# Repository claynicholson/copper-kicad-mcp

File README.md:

<!-- mcp-name: io.github.claynicholson/copper -->
# copper-kicad-mcp

Copper connects your AI app to KiCad, so it can design real boards you can order: schematic, LCSC parts, PCB
layout and routing, KiCad's own ERC and DRC, renders and JLCPCB fab files.

## Install

You need [KiCad 10](https://www.kicad.org/download/). Then pick one:

| You use | Do this |
|---|---|
| Windows, any AI app | Run `Copper-for-KiCad-1.1.1-Setup.exe` from the [latest release](https://github.com/claynicholson/copper-kicad-mcp/releases/latest) and tick your AI apps |
| Claude Desktop | Double-click `copper-1.1.1.mcpb` from the [latest release](https://github.com/claynicholson/copper-kicad-mcp/releases/latest) |
| Claude Code | The two plugin commands below |
| Cursor, VS Code, Windsurf, Codex, Zed and others | `npx -y copper-kicad setup` (Node.js 18+), or [add to Cursor](https://cursor.com/install-mcp?name=copper&config=eyJjb21tYW5kIjoibnB4IiwiYXJncyI6WyIteSIsImNvcHBlci1raWNhZCJdfQ%3D%3D) / [install in VS Code](https://vscode.dev/redirect/mcp/install?name=copper&config=%7B%22command%22%3A%22npx%22%2C%22args%22%3A%5B%22-y%22%2C%22copper-kicad%22%5D%7D) |
| A terminal | The one-line installer below |

```sh
# Claude Code
claude plugin marketplace add claynicholson/copper-kicad-mcp
claude plugin install copper@copper
```

```powershell
# Windows (PowerShell)
powershell -ExecutionPolicy Bypass -c "irm https://raw.githubusercontent.com/claynicholson/copper-kicad-mcp/main/installer/install.ps1 | iex"
```

```sh
# macOS / Linux
curl -LsSf https://raw.githubusercontent.com/claynicholson/copper-kicad-mcp/main/installer/install.sh | sh
```

Windows is tested end to end. The macOS and Linux routes are new: if one fails, please
[open an issue](https://github.com/claynicholson/copper-kicad-mcp/issues).

Setup finds KiCad, brings your libraries and settings along, connects your AI apps and makes a test call. It asks
before each step and backs up everything it changes. To paste a config instead, Cursor, Claude Desktop and Windsurf
take this entry ([docs/INSTALL.md](docs/INSTALL.md) has the others):

```json
{ "mcpServers": { "copper": { "command": "npx", "args": ["-y", "copper-kicad"] } } }
```

`npx -y copper-kicad setup --demo` runs the setup page on a throw-away folder, so you can look first. If something
does not work, `npx -y copper-kicad doctor` (or `copper doctor` after the Windows or one-line install) names the
fix. More in [docs/INSTALL.md](docs/INSTALL.md).

## What it does

Ask for something like "Design a USB-C powered ESP32-C3 board with a status LED, 30 x 40 mm". Your AI then works
through it the way an engineer would:

- It connects pins to nets by name (`U1.PA9 → USB_DP`), never by coordinates.
- It searches LCSC/JLCPCB for real parts (Basic parts first, live stock) and imports each part's symbol and
  footprint, plus its 3D model when EasyEDA has one.
- KiCad's ERC and DRC re-run after every change, and each finding comes with a ready fix.
- It places parts and routes the board: a staged router with length matching, differential pairs and width
  classes, copper pours, and Freerouting.
- It looks at its work: schematic, layer and ray-traced 3D renders go back to the model.
- It writes Gerbers, drill, BOM and placement files for JLCPCB (or PCBWay, OSH Park, generic), zipped.

Copper has 31 tools and works with any MCP app and any model. The model is your AI app's: the Copper server never
calls one.

## Boards made with Copper

<table>
<tr>
<td width="33%"><br>RP2040 Macropad: nine hot-swap keys and a knob. 66 x 90 mm, 2 layers, 65 parts.</td>
<td width="33%"><br>RP2040 D-pad E-ink: D-pad, e-ink FPC and IMU. 72 x 84 mm, 4 layers, 55 parts.</td>
<td width="33%"><br>Stepper G0: a 12 V stepper controller on one board. 58 x 48 mm, 2 layers, 40 parts.</td>
</tr>
<tr>
<td width="33%"><br>ESP32-C3 USB-C: Wi-Fi and BLE on USB-C. 30 x 40 mm, 2 layers, 15 parts.</td>
<td width="33%"><br>USB-C Power Bank: an IP5306 power bank with USB-C in. 50 x 24 mm, 2 layers, 22 parts.</td>
<td width="33%"><br>Phone Breathalyzer: an alcohol sensor that plugs into a phone. 22 x 48 mm, 2 layers, 30 parts.</td>
</tr>
</table>

All six pass KiCad 10's ERC and DRC with 0 errors and 0 unconnected items. Layer art and fab files (Gerbers,
drill, BOM, placement) are on [coppereda.com](https://coppereda.com).

## Docs

[Install](docs/INSTALL.md) · [Configuration](docs/CONFIG.md) · [Parts providers](docs/PROVIDERS.md) ·
[Fab profiles](docs/FAB_PROFILES.md) · [KiCad compatibility](docs/COMPATIBILITY.md) ·
[Architecture](docs/ARCHITECTURE.md) · [Changelog](CHANGELOG.md) · [Contributing](CONTRIBUTING.md) · [Security](SECURITY.md)

## Privacy

Copper runs on your machine. Your designs stay there, and there is no telemetry. It goes online only to:

- search and download parts: LCSC, JLCPCB and EasyEDA, with the jlcsearch.tscircuit.com mirror as a fallback
- check for a newer KiCad (gitlab.com) during `setup` and `doctor`; `COPPER_NO_UPDATE_CHECK=1` turns that off
- download Freerouting (GitHub) and a Java runtime (Adoptium), about 120 MB once, when you ask for autorouting
- sign in to GitHub, if you link it without the GitHub CLI

Installing fetches a little more: the `npx` launcher installs Pillow from PyPI if KiCad's Python lacks it, and the
one-line installers fetch [uv](https://docs.astral.sh/uv/), a Python 3.12 build and Pillow.

The MCP server and CLI never call a language model. The package also holds `copper_kicad.agent`, a chat sidecar for
a separate desktop app; nothing in the server or CLI starts it.

## License

[MIT](LICENSE). Copper is an independent project, not affiliated with KiCad, LCSC, JLCPCB or any other vendor named here.

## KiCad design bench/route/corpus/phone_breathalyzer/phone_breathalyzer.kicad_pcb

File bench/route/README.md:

# Routing benchmark

Objective scoring of a PCB autorouter on real, human-routed KiCad boards (plus two synthetic stress cases).
KiCad itself is the judge: completion and DRC come from `kicad-cli pcb drc` on the routed board, length /
vias / widths from pcbnew. Nothing a router reports about itself is trusted for the score.

```
PY="C:/Program Files/KiCad/10.0/bin/python.exe"            # KiCad's Python (has Pillow)
$PY bench/route/prepare.py [--force] [--only NAME]         # (re)build corpus/ from the KiCad demos — already done
$PY bench/route/run.py --router guided --list              # the corpus
$PY bench/route/run.py --router guided                     # all boards, 2 runs each (determinism)
$PY bench/route/run.py --router guided --board stickhub    # one board
$PY bench/route/run.py --router freerouting --runs 1       # Freerouting (needs the Java + jar Copper downloaded)
$PY bench/route/run.py --router v2 --name v2-try3 --opt plan='{"global":{"via_cost":8}}'
$PY bench/route/run.py --router guided --summarize         # rebuild results/guided.md from results/guided/*.json
$PY bench/route/run.py --router v2 --suite cons --name cons_A      # the constraint boards (length groups, pairs, keep-short)
$PY bench/route/run.py --router v2 --suite cons --name cons_A_off --opt plan='{"global":{"constraints":"off"}}'
#   (results/constraints_baseline.md = before any tuning; results/constraints_tune.md = length tuning, before / after per group;
#    results/constraints_final.md = coupled pairs, skew, widths, keep-short: the four boards, the gate and the 14-board corpus;
#    results/constraints_fix1.md = after the independent verification: the six failures before / after, suite, gate, corpus;
#    results/constraints_fix2.md = after the second verification: the two failures before / after, suite, gate, corpus)
$PY bench/route/diagnose.py guided [board ...]             # failure-mode digest
$PY bench/route/steer_demo.py coldfire --rule order --base v2_stage7   # one plan revision from the router's own suggest[], before / after
```

Boards can be run in parallel in separate processes (one `--board` each); every process rewrites the
summary from the per-board files, so finish with `--summarize`.

`--suite route` (the default) is the 14-board corpus: its table and totals are comparable from run to run.
`--suite cons` (alias `--group constraints`) is the four constraint boards, `--suite all` both; a `--board` named
explicitly runs whatever its suite. Constraint boards get their own section in `results/<name>.md` and never count
in the corpus totals. When `results/<name>_off/` exists (the same boards with `global.constraints: "off"`), it
supplies the wall-time limit of the verdict.

## Files

| | |
|---|---|
| `corpus/<board>/<board>.kicad_pcb` | UNROUTED copy (tracks + vias + teardrops removed, zones refilled, footprints and rules kept) |
| `corpus/<board>/<board>.kicad_pro`, `.kicad_dru` | the original's net classes / design rules |
| `corpus/<board>/meta.json` | facts (layers, pads, pitch, per-net MST), the human reference (total + per-net length, vias, widths, layers, DRC of the original) and the DRC of the unrouted board |
| `corpus/<board>/reference.json` | the human routing as segments + vias (for the reference picture) |
| `results/<name>/<board>.json` | every measured number of every run + the router's own report |
| `results/<name>/<board>.png`, `.human.png` | the routed result (yellow = still unconnected) and the reference |
| `results/<name>.md`, `.json` | the table |
| `routers/<name>.py` | router adapters (`guided`, `freerouting`, `none`); see `routers/__init__.py` for the 3-function interface |
| `corpus/cons_*/` | constraint boards: synthetic, with net classes in `.kicad_pro`, KiCad custom rules in `.kicad_dru` (skew, pair gap, uncoupled length, max length) and the expected constraint set + thresholds in `meta.json` (`"suite": "cons"`, `"constraints"`) |
| `cons.py` | constraint metrics and the pass / fail verdict (design §14.11); `common.kicad_lengths()` asks KiCad for every net's length |
| `cons_probe.py` | what KiCad's own DRC says about length / skew / pair rules on tiny hand-made boards (the facts the design rests on) |
| `.work/` | scratch: run copies, a private KiCad config dir, a private COPPER_HOME, temp files (git-ignored) |

## What is measured

* **done %** = (connections on the unrouted board − KiCad's unconnected count after routing) / connections.
  Nets a router decides to skip (e.g. GND "left for a pour") count as not done.
* **DRC err (new)** = all kicad-cli errors with zones refilled; `new` = not on the unrouted board (multiset
  difference on type + text + items), i.e. caused by the routing.
* **len ×** = total track length / the reference's. **common ×** = the same over nets that are complete in
  both and carry tracks in both (like for like; pours make whole-board totals misleading).
* per result JSON also: per-net worst detours, extra vias, nets routed thinner than the reference's
  dominant width, length / MST, share of segments that are not on a 45° direction, share shorter than 0.2 mm.
* **same twice** = two routes of two fresh copies give item-for-item identical copper (1 µm).
* **wall s** = the router call only (not the harness's own measure + DRC).

## Constraint boards (suite `cons`)

| board | what a router has to get right | KiCad rules in its `.kicad_dru` |
|---|---|---|
| `cons_usb_pair` | a USB pair, connector to MCU with a 90 degree turn; class gap 0.15 mm, below the 0.2 mm clearance | skew <= 0.15; pair gap 0.15 .. 0.9; uncoupled <= 6 |
| `cons_bus_match` | SD bus, 4 data + clock, natural lengths about 8 mm apart | skew <= 0.5 over the five nets |
| `cons_pairs_cross` | two pairs that must cross on SMD pads (connectors at the board edge) | per pair: skew <= 0.2; gap 0.15 .. 1.2; uncoupled <= 8 |
| `cons_mixed` | 4 layers: QSPI group, USB pair, crystal, 12 plain nets, plane on In1 | QSPI skew <= 0.3; the USB rules; crystal legs <= 8 mm |

The rules are skew / pair / max-length rules on purpose: KiCad leaves those silent on a net without tracks, so the
unrouted boards carry no constraint error (`prepare.py` refuses to build one that does).

Measured per board, from the routed file and KiCad alone:

* **KiCad lengths** of every constrained net: a copy of the routed board gets one rule no net can meet
  (`length (min 100000mm)`); the "actual" in each DRC message is KiCad's figure (tracks, in-pad and in-via
  shortcut, via height, pad-to-die).
* **group spread** = longest - shortest member against the tolerance; **pair skew**; **vias P / N**;
  **coupled %** = share of the longer net's track length with a parallel segment of the other net on the same
  layer at the pair's gap +- 0.02 mm; **keep-short** length against its maximum.
* **new DRC** includes KiCad's five constraint error types; they are also listed by type.
* **len model err** = largest |router's own length figure - KiCad's| (the one number that reads the router's report);
  **detection** = what the router finds on the unrouted board with no plan, against `meta.constraints`.

A board passes only when every threshold holds (done 100 %, 0 new DRC, same twice, detection exact, len model err
<= 0.005 mm, spread <= tol, skew <= rule, coupled % >= the board's minimum, vias P = N, wall <= 1.5 x the `off`
run + 10 s). A miss is reported with its amount; the rule files are not loosened.

## Adding a router

Create `routers/v2.py` with `NAME`, `available()` and `route(project_dir, pcb, options) -> dict`. It gets a
private copy of the unrouted board and must leave the routed board in the same file. Then
`run.py --router v2`. The harness sandboxes `KICAD_CONFIG_HOME`, `COPPER_HOME` and the temp dir under
`.work/` before the router is imported.

## Caveats

* The reference for `phone_breathalyzer` is whatever routing is on that board today, not a hand layout.
* Humans often rely on pours for power; the unrouted copies keep the zones, so a router has the same pours.
* `one_air_max`, `tinytapeout` and `cm5_minima` carry DRC errors on the UNROUTED board (footprint-level:
  see `meta.json`), which is why `new` is the column to watch.
* The corpus is ~16 MB of board files regenerated by `prepare.py` from a KiCad 10 install.

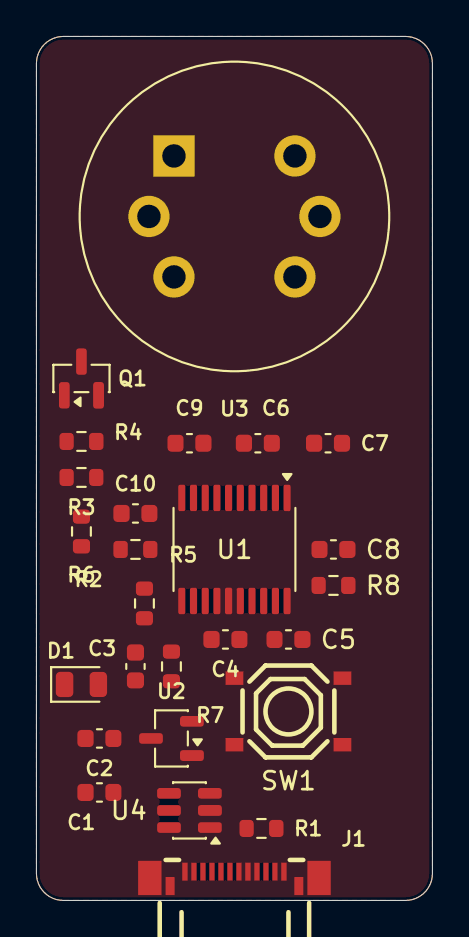
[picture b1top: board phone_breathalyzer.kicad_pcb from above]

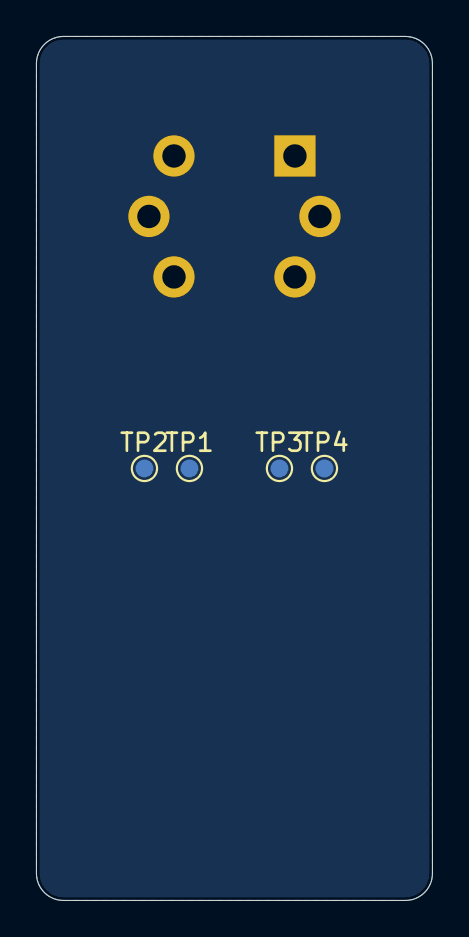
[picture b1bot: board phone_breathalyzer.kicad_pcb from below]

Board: 2 copper layers, 22.0 x 48.0 mm, 30 parts (4 on the bottom side), 17 nets, no tracks yet.

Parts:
C1, C5: 4.7uF; C_0603_1608Metric
C2, C3, C7: 1uF; C_0603_1608Metric
C4, C6, C8, C9, C10: 100nF; C_0603_1608Metric
D1: LED green; LED_0805_2012Metric
J1: TYPE-C-31-G-03; USB-C-SMD_TYPE-C-31-G-03_edge
Q1: AO3400A; SOT-23
R1: 5.1k; R_0603_1608Metric
R2, R8: 10k; R_0603_1608Metric
R3: 100R; R_0603_1608Metric
R4, R5, R6: 100k; R_0603_1608Metric
R7: 1k; R_0603_1608Metric
SW1: TS-1187A-B-A-B; SW-SMD_4P-L5.1-W5.1-P3.70-LS6.5-TL_H1.5
TP1: SWDIO; TestPoint_Pad_D1.0mm
TP2: SWCLK; TestPoint_Pad_D1.0mm
TP3: NRST; TestPoint_Pad_D1.0mm
TP4: GND; TestPoint_Pad_D1.0mm
U1: STM32F042F6P6; TSSOP-20_4.4x6.5mm_P0.65mm
U2: XC6206P332MR-G; SOT-23-3
U3: MQ-3B; MQ-3B_drill1.3
U4: USBLC6-2SC6; SOT-23-6

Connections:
+3V3: C3.1, C4.1, C5.1, C6.1, C7.1, SW1.1 (A), U1.5 (VDDA), U1.16 (VDD), U2.2 (VO), U3.4 (A2), U3.6 (A1)
/ALC_SENSE: C9.1, R2.1, U1.6 (PA0), U3.1 (B1), U3.3 (B2)
/BOOT0: R8.1, SW1.4 (D), U1.1 (PB8)
/CC: J1.A5 (CC1), R1.1
/HEAT_EN: R3.1, U1.10 (PA4)
/HEAT_GATE: Q1.1 (G), R3.2, R4.1
/HEAT_SW: Q1.3 (D), U3.5 (VH-)
/LED: R7.1, U1.11 (PA5)
/LED_A: D1.2 (A), R7.2
/NRST: C8.1, TP3.1 (1_1), U1.4 (NRST)
/SUPPLY_SENSE: C10.1, R5.2, R6.1, U1.7 (PA1)
/SWCLK: TP2.1 (1_1), U1.20 (PA14)
/SWDIO: TP1.1 (1_1), U1.19 (PA13)
/USB_DM: J1.A7 (DN1), U1.17 (PA9/PA11), U4.3 (I/O2), U4.4 (I/O2)
/USB_DP: J1.A6 (DP1), U1.18 (PA10/PA12), U4.1 (I/O1), U4.6 (I/O1)
GND: C1.2, C2.2, C3.2, C4.2, C5.2, C6.2, C7.2, C8.2, C9.2, C10.2, D1.1 (K), J1.13 (GND), J1.14 (GND), J1.15 (GND), J1.16 (GND), J1.A1 (GND), J1.A12 (GND), J1.B12 (GND), Q1.2 (S), R1.2, R2.2, R4.2, R6.2, R8.2, TP4.1 (1_1), U1.15 (VSSA), U2.1 (GND), U4.2 (GND)
VBUS: C1.1, C2.1, J1.A4 (VBUS), J1.B9 (VBUS), R5.1, U2.3 (VI), U3.2 (VH+), U4.5 (VBUS)

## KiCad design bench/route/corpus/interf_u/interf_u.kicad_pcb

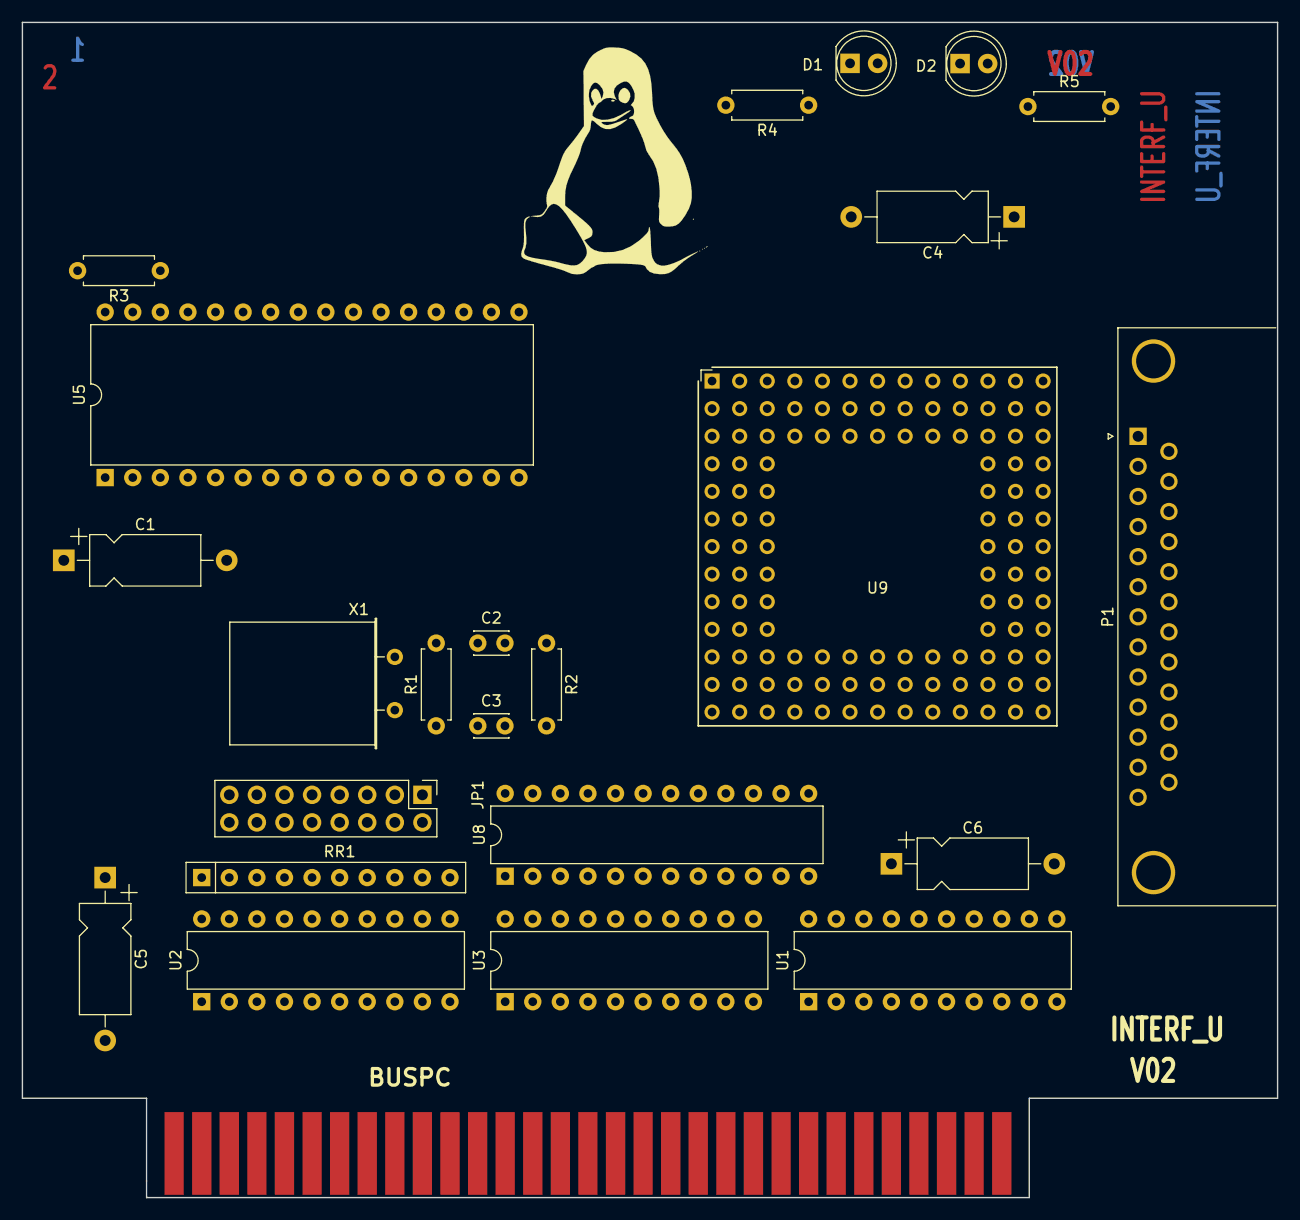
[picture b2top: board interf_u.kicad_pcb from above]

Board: 2 copper layers, 115.6 x 108.2 mm, 25 parts (0 on the bottom side), 110 nets, no tracks yet.

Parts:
BUS1: BUSPC; BUS_PC
C1, C4, C5, C6: 47uF; CP_Axial_L10.0mm_D4.5mm_P15.00mm_Horizontal
C2, C3: 47pF; C_Disc_D3.0mm_W2.0mm_P2.50mm
D1, D2: LED; LED_D5.0mm
G1: LOGO; tux
JP1: CONN_8X2; PinHeader_2x08_P2.54mm_Vertical
P1: DB25FEMELLE; DSUB-25_Female_Horizontal_P2.77x2.84mm_EdgePinOffset9.90mm_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
R1: 100K; R_Axial_DIN0207_L6.3mm_D2.5mm_P7.62mm_Horizontal
R2: 1K; R_Axial_DIN0207_L6.3mm_D2.5mm_P7.62mm_Horizontal
R3: 10K; R_Axial_DIN0207_L6.3mm_D2.5mm_P7.62mm_Horizontal
R4, R5: 330; R_Axial_DIN0207_L6.3mm_D2.5mm_P7.62mm_Horizontal
RR1: 9x1K; R_Array_SIP10
U1: 74LS245; DIP-20_W7.62mm
U2: 74LS688; DIP-20_W7.62mm
U3: 74LS541; DIP-20_W7.62mm
U5: 628128; DIP-32_W15.24mm
U8: EP600; DIP-24_W7.62mm
U9: 4003APG120; PGA120
X1: 8MHz; Crystal_HC18-U_Horizontal

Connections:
/8MH-OUT: R2.1, U9.K1 (P/A5)
/ACK: P1.10, U9.K13
/AUTOFD-: P1.14, U9.C12 (PGCK2)
/BIT0: P1.2, U9.D12
/BIT1: P1.3, U9.E13
/BIT2: P1.4, U9.F12
/BIT3: P1.5, U9.G13
/BIT4: P1.6, U9.H13
/BIT5: P1.7, U9.H12
/BIT6: P1.8, U9.J13
/BIT7: P1.9, U9.H11
/BUST+: P1.11, U9.J12
/CLKLCA: U8.16 (I/O16), U9.L4 (CCLK), U9.M4 (NC)
/CS1-: U5.22 (CS1), U9.A10
/D0: U1.18 (B0), U8.21 (I/O21), U9.N2 (DIN)
/D1: U1.17 (B1), U9.N8
/D2: U1.16 (B2), U9.N9
/D3: U1.15 (B3), U9.M9 (P/D5)
/D4: U1.14 (B4), U9.M10 (P/D6)
/D5: U1.13 (B5), U9.N11
/D6: U1.12 (B6), U9.M11 (P/D7)
/D7: U1.11 (B7), U9.L12 (SGCK3)
/DIR: U1.1 (A->B), U8.17 (I/O17)
/DONE: U8.20 (I/O20), U9.L11 (DONE)
/ENBBUF: U1.19 (CE), U8.22 (I/O22)
/ERROR-: P1.15, U9.D13
/INIT-: P1.16, U9.E12
/LED1: R4.2, U9.M3 (DOUT-SGKC4)
/LED2: R5.2, U9.F13 (INIT)
/MA0: U5.12 (A0), U9.A11
/MA1: U5.11 (A1), U9.B2 (PGCK1/A16)
/MA2: U5.10 (A2), U9.D3 (SGCK1)
/MA3: U5.9 (A3), U9.C2 (P/A14)
/MA4: U5.8 (A4), U9.E1
/MA5: U5.7 (A5), U9.C13 (LDC)
/MA6: U5.6 (A6), U9.F2
/MA7: U5.5 (A7), U9.B3 (P/A17)
/MA8: U5.27 (A8), U9.G1 (P/A8)
/MA9: U5.26 (A9), U9.A4
/MA10: U5.23 (A10), U9.C9
/MA11: U5.25 (A11), U9.D2 (P/A13)
/MA12: U5.4 (A12), U9.F3 (P/A10)
/MA13: U5.28 (A13), U9.C1 (P/A12)
/MA14: U5.3 (A14), U9.D1 (P/A11)
/MA15: U5.31 (A15), U9.F1 (P/A9)
/MA16: U5.2 (A16), U9.C8
/MATCHL: U2.19 (P=R), U8.2 (IN2)
/MD0: U5.13 (Q0), U9.C6
/MD1: U5.14 (Q1), U9.A5
/MD2: U5.15 (Q2), U9.B6
/MD3: U5.17 (Q3), U9.A6
/MD4: U5.18 (Q4), U9.A7
/MD5: U5.19 (Q5), U9.A8
/MD6: U5.20 (Q6), U9.A9
/MD7: U5.21 (Q7), U9.B8
/OE-: U5.24 (OE), U9.B9
/PC-A0: BUS1.62 (BA00), U3.3 (A1), U9.M6
/PC-A1: BUS1.61 (BA01), U3.2 (A0), U9.N4
/PC-A2: BUS1.60 (BA02), U3.4 (A2), U9.M5 (P/D1)
/PC-A3: BUS1.59 (BA03), U3.5 (A3), U9.K2 (P/CS1/A2)
/PC-A4: BUS1.58 (BA04), U2.17 (P7), U9.H3
/PC-A5: BUS1.57 (BA05), U2.2 (P0), U9.J2 (P/A4)
/PC-A6: BUS1.56 (BA06), U2.15 (P6), U9.J1
/PC-A7: BUS1.55 (BA07), U2.13 (P5), U9.H2 (P/A6)
/PC-A8: BUS1.54 (BA08), U2.4 (P1), U9.H1 (P/A7)
/PC-A9: BUS1.53 (BA09), U2.6 (P2), U9.N7 (P/D3)
/PC-A10: BUS1.52 (BA10), U2.11 (P4), U9.L8
/PC-A11: BUS1.51 (BA11), U2.8 (P3)
/PC-AEN: BUS1.42 (AEN), U2.1 (G), U9.N10 (P/CS0)
/PC-DB0: BUS1.40 (DB0), U1.2 (A0)
/PC-DB1: BUS1.39 (DB1), U1.3 (A1)
/PC-DB2: BUS1.38 (DB2), U1.4 (A2)
/PC-DB3: BUS1.37 (DB3), U1.5 (A3)
/PC-DB4: BUS1.36 (DB4), U1.6 (A4)
/PC-DB5: BUS1.35 (DB5), U1.7 (A5)
/PC-DB6: BUS1.34 (DB6), U1.8 (A6)
/PC-DB7: BUS1.33 (DB7), U1.9 (A7)
/PC-IOR: BUS1.14 (IOR), U3.7 (A5)
/PC-IOW: BUS1.13 (IOW), U3.6 (A4)
/PC-RD: U3.13 (Y5), U8.14 (IN14), U9.M8 (P/D4)
/PC-RST: BUS1.2 (RESET), U3.8 (A6), U3.9 (A7)
/PC-WR: U3.14 (Y4), U8.7 (I/O7), U9.N6 (P/RS)
/PE+: P1.12, U9.L13
/PROG-: U8.19 (I/O19), U9.M12 (PROG)
/REF4: JP1.14, RR1.3, U2.18 (R7)
/REF5: JP1.16, RR1.2, U2.3 (R0)
/REF6: JP1.10, RR1.5, U2.16 (R6)
/REF7: JP1.6, RR1.7, U2.14 (R5)
/REF8: JP1.12, RR1.4, U2.5 (R1)
/REF9: JP1.8, RR1.6, U2.7 (R2)
/REF10: JP1.2, RR1.9, U2.12 (R4)
/REF11: JP1.4, RR1.8, U2.9 (R3)
/RSTL: U3.12 (Y6), U8.11 (IN11)
/SEL_LPT: U8.18 (I/O18), U9.L2 (P/A0/WS)
/SLCT+: P1.13, U9.N13 (PGCK3)
/SLCTIN-: P1.17, U9.F11
/STROBE: P1.1, U9.A12 (SGCK2)
/WR-: U5.29 (WR), U9.A13 (HDC)
/WR_REG: U8.13 (CLK2), U8.15 (I/O15)
GND: BUS1.1 (GND), BUS1.31 (GND), C1.2, C2.2, C3.2, C4.2, C5.2, C6.2, D1.1 (K), D2.1 (K), JP1.1, JP1.3, JP1.5, JP1.7, JP1.9, JP1.11, JP1.13, JP1.15, P1.18, P1.19, P1.20, P1.21, P1.22, P1.23, P1.24, P1.25, U1.10 (GND), U2.10 (GND), U3.1 (G1), U3.10 (GND), U3.19 (G2), U5.16 (GND), U8.1 (CLK1), U8.12 (GND), U9.B7 (GND), U9.C4 (GND), U9.C10 (GND), U9.G2 (GND), U9.G11 (GND), U9.K3 (GND), U9.K11 (GND), U9.L7 (GND)
unnamed: C3.1, R1.1, R2.2, X1.2
unnamed: D1.2 (A), R4.1
unnamed: D2.2 (A), R5.1
unnamed: U3.18 (Y0), U8.3 (I/O3)
unnamed: U3.17 (Y1), U8.4 (I/O4)
unnamed: U3.16 (Y2), U8.5 (I/O5)
unnamed: U3.15 (Y3), U8.6 (I/O6)
unnamed: R3.1, U5.30 (CS2)
unnamed: C2.1, R1.2, U9.L1 (P/A3), X1.1
VCC: BUS1.3 (VCC), BUS1.29 (VCC), C1.1, C4.1, C5.1, C6.1, R3.2, RR1.1 (COM), U1.20 (VCC), U2.20 (VCC), U3.20 (VCC), U5.32 (VCC), U8.23 (IN23), U8.24 (VCC), U9.B11 (M1), U9.B12 (M2), U9.C3 (VCC), U9.C11 (M0), U9.D11 (VCC), U9.G12 (VCC), U9.L3 (VCC), U9.L10 (VCC), U9.M7 (VCC)

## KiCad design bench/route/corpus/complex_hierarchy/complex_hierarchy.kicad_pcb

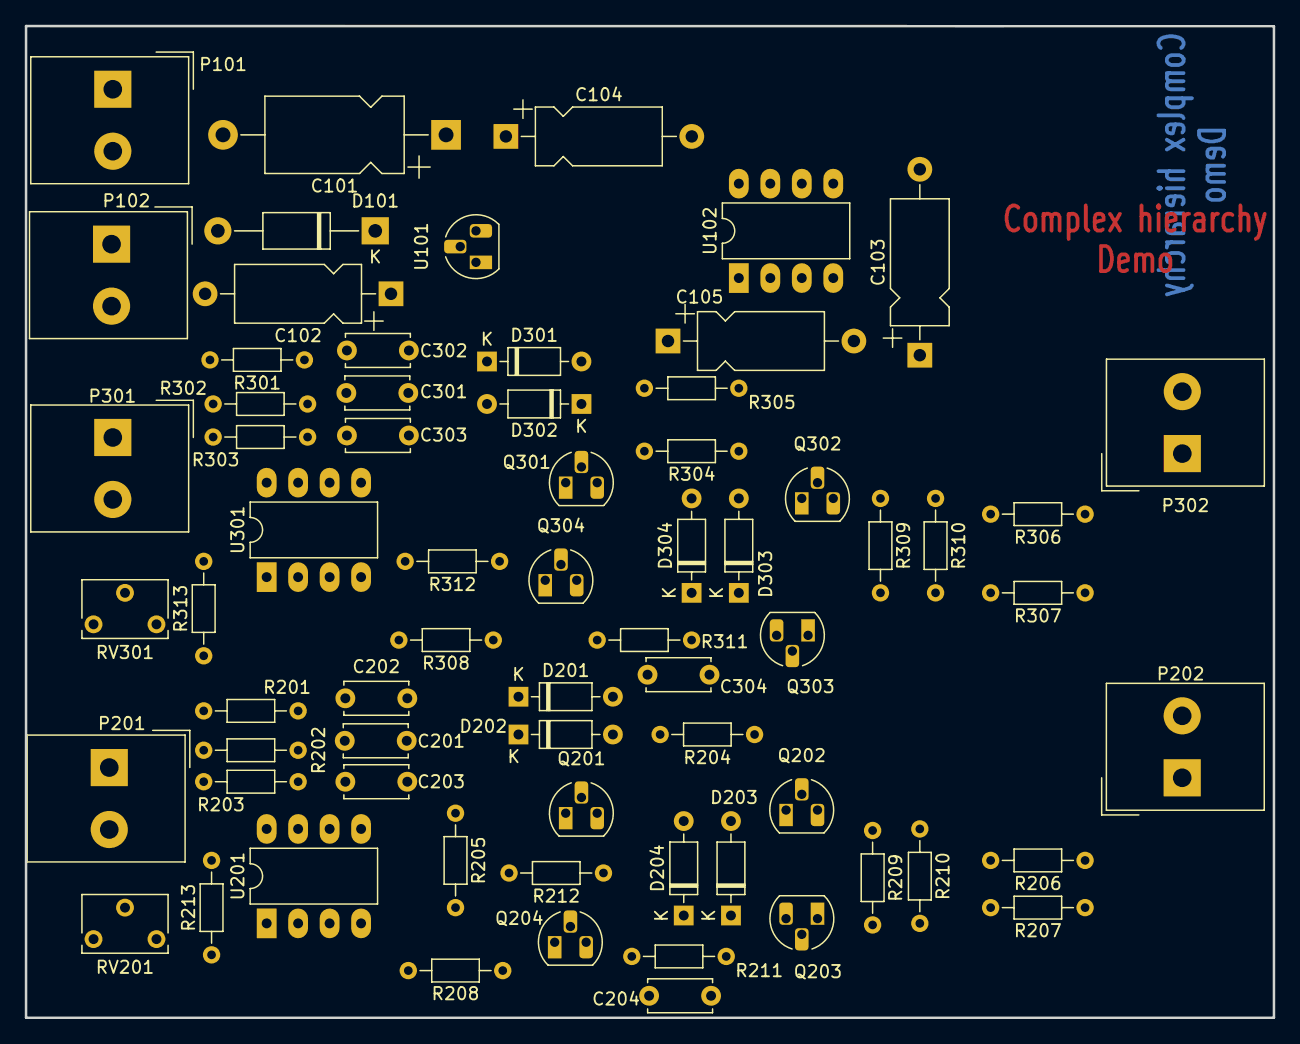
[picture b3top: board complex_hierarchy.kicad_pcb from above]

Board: 2 copper layers, 100.7 x 80.0 mm, 68 parts (0 on the bottom side), 50 nets, no tracks yet.

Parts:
C101: 47uF/63V; CP_Axial_L11.0mm_D6.0mm_P18.00mm_Horizontal
C102: 47uF; CP_Axial_L10.0mm_D4.5mm_P15.00mm_Horizontal
C103, C105: 10uF; CP_Axial_L10.0mm_D4.5mm_P15.00mm_Horizontal
C104: 47uF/20V; CP_Axial_L10.0mm_D4.5mm_P15.00mm_Horizontal
C201, C301: 15nF; C_Disc_D5.0mm_W2.5mm_P5.00mm
C202, C302: 150nF; C_Disc_D5.0mm_W2.5mm_P5.00mm
C203, C303: 4.7nF; C_Disc_D5.0mm_W2.5mm_P5.00mm
C204, C304: 820pF; C_Disc_D5.0mm_W2.5mm_P5.00mm
D101: 1N4007; D_DO-41_SOD81_P12.70mm_Horizontal
D201, D202, D203, D204, D301, D302, D303, D304: 1N4148; D_DO-35_SOD27_P7.62mm_Horizontal
P101, P102, P201, P202, P301, P302: CONN_2; Altech_AK300_1x02_P5.00mm_45-Degree
Q201, Q203, Q301, Q303: MPSA92; TO-92_HandSolder
Q202, Q204, Q302, Q304: MPSA42; TO-92_HandSolder
R201, R208, R212, R301, R308, R312: 1K; R_Axial_DIN0204_L3.6mm_D1.6mm_P7.62mm_Horizontal
R202, R203, R302, R303: 22K; R_Axial_DIN0204_L3.6mm_D1.6mm_P7.62mm_Horizontal
R204, R304: 470; R_Axial_DIN0204_L3.6mm_D1.6mm_P7.62mm_Horizontal
R205, R209, R210, R305, R309, R310: 220K; R_Axial_DIN0204_L3.6mm_D1.6mm_P7.62mm_Horizontal
R206, R207, R306, R307: 47; R_Axial_DIN0204_L3.6mm_D1.6mm_P7.62mm_Horizontal
R211, R311: 5,6K; R_Axial_DIN0204_L3.6mm_D1.6mm_P7.62mm_Horizontal
R213, R313: 4,7K; R_Axial_DIN0204_L3.6mm_D1.6mm_P7.62mm_Horizontal
RV201, RV301: 4,7K; Potentiometer_Bourns_3266W_Vertical
U101: 78L05; TO-92_HandSolder
U102: ICL7660; DIP-8_W7.62mm_LongPads
U201, U301: LM358N; DIP-8_W7.62mm_LongPads

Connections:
+12V: C104.1, D101.1 (K), U101.3 (VI), U201.8 (V+), U301.8 (V+)
-VAA: C103.2, U102.5 (VOUT), U201.4 (V-), U301.4 (V-)
/12Vext: D101.2 (A), P102.1
/ampli_ht_horizontal/PIEZO_IN: P301.1, R301.2
/ampli_ht_horizontal/PIEZO_OUT: P302.1, R306.1, R307.1
/ampli_ht_horizontal/S_OUT+: R309.1, R310.1, RV301.3
/ampli_ht_horizontal/Vpil_0_3,3V: C301.1, U301.3 (+), U301.6 (-), U301.7
/ampli_ht_vertical/PIEZO_IN: P201.1, R201.2
/ampli_ht_vertical/PIEZO_OUT: P202.1, R206.1, R207.1
/ampli_ht_vertical/S_OUT+: R209.1, R210.1, RV201.3
/ampli_ht_vertical/Vpil_0_3,3V: C201.1, U201.3 (+), U201.6 (-), U201.7
GND: C101.2, C102.2, C103.1, C104.2, C202.2, C203.2, C204.2, C302.2, C303.2, C304.2, P101.2 (PM), P102.2 (PM), P201.2 (PM), P202.2 (PM), P301.2 (PM), P302.2 (PM), Q203.3 (C), Q303.3 (C), R205.2, R208.2, R213.2, R305.2, R308.2, R313.2, U101.2 (GND), U102.3 (GND)
HT: C101.1, D201.2 (A), D301.2 (A), P101.1, Q202.3 (C), Q302.3 (C), R204.1, R304.1
unnamed: C201.2, R202.1, R203.2
unnamed: C202.1, R201.1, R202.2
unnamed: C204.1, R211.2
unnamed: C301.2, R302.1, R303.2
unnamed: C302.1, R301.1, R302.2
unnamed: C304.1, R311.2
unnamed: D201.1 (K), D202.2 (A)
unnamed: D202.1 (K), Q201.2 (B), R205.1
unnamed: D203.2 (A), Q201.3 (C), Q202.2 (B)
unnamed: D203.1 (K), D204.2 (A)
unnamed: D204.1 (K), Q203.2 (B), Q204.3 (C), R211.1
unnamed: D301.1 (K), D302.2 (A)
unnamed: D302.1 (K), Q301.2 (B), R305.1
unnamed: D303.2 (A), Q301.3 (C), Q302.2 (B)
unnamed: D303.1 (K), D304.2 (A)
unnamed: D304.1 (K), Q303.2 (B), Q304.3 (C), R311.1
unnamed: Q201.1 (E), R204.2
unnamed: Q202.1 (E), R206.2, R210.2
unnamed: Q203.1 (E), R207.2, R209.2
unnamed: Q204.2 (B), R208.1
unnamed: Q204.1 (E), R212.1
unnamed: Q301.1 (E), R304.2
unnamed: Q302.1 (E), R306.2, R310.2
unnamed: Q303.1 (E), R307.2, R309.2
unnamed: Q304.2 (B), R308.1
unnamed: Q304.1 (E), R312.1
unnamed: R212.2, U201.1
unnamed: R213.1, RV201.1
unnamed: R312.2, U301.1
unnamed: R313.1, RV301.1
unnamed: C105.1, U102.2 (CAP+)
unnamed: C105.2, U102.4 (CAP-)
unnamed: RV201.2, U201.2 (-)
unnamed: C203.1, R203.1, U201.5 (+)
unnamed: RV301.2, U301.2 (-)
unnamed: C303.1, R303.1, U301.5 (+)
VCC: C102.1, U101.1 (VO), U102.8 (V+)
